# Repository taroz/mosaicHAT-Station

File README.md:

# mosaicHAT-Station
## Introduction
- [**mosaicHAT**](https://github.com/septentrio-gnss/mosaicHAT) + **GNSS antenna** + **Raspberry Pi** + **Touch display** + **Battery** + **Case**
- We use [Septentrio's mosaic-X5](https://www.septentrio.com/en/products/gnss-receivers/rover-base-receivers/receivers-module/mosaic) GNSS module which is a **low-cost** and **survey-grade** GNSS receiver
- This project is inspired by [mosaicHAT](https://github.com/septentrio-gnss/mosaicHAT) and extends it further. Thanks to the wonderful project [mosaicHAT](https://github.com/septentrio-gnss/mosaicHAT)!
- License: [Creative Commons Attribution Share-Alike License](https://creativecommons.org/licenses/by-sa/4.0/). and [Open Source HW](https://www.oshwa.org/definition/)  

## Features
- mosaicHAT Station has a touch display to display a web user interface of mosaic-X5 receiver. We can easily operate, monitor, and control the GNSS receiver.
- Compared to the original [mosaicHAT](https://github.com/septentrio-gnss/mosaicHAT), we added micro SD card and a log button, so you can easily store GNSS data as a GNSS reference or rover station.  

## Board
- The design of the board is based on the original [mosaicHAT](https://github.com/septentrio-gnss/mosaicHAT).
- [KiCAD files](./board/KiCAD) and [PCB](./board/KiCAD/pcb)
- Micro SD card and log button have been added for data logging capability
- Bill of Materials (BOM) is [here](./board/mosaicHAT_BOM.xlsx)                                 

## Case
- You can create using 3D printer (STL data is [here](./case))
  - I used 3D printing service (by [Shapeways](https://www.shapeways.com/shops/tarosuzuki)) 
- A 5/8 nut can be fixed on the case, which can be attached to a pole or antenna mount for GNSS surveying.  

## How to assemble
- Parts list is [here](./case/parts_list.xlsx)  
<p>

1. Mount the Raspberry Pi on the touch display. Then mount the mosaicHAT on the Rasberry Pi using the M2.5 18mm spacers and screws.   
<p>

2. Fix the GNSS antenna using the M2.5 screws. Connect the SMA cable. Mount the touch display on the case using the M2.5 screws.   
<p>

3. Modify the battery holder to connect the DCDC converter to the battery. Fix the battery holder to the back plate. Then connect the power cable to the mosaicHAT. Fix the front plate using the M3 screws.  
<p>

4. Finally, fix the front and back plate using M3 50mm screws. Insert the W5/8 nut to bottom plate. Fix the bottom plate to the case.   
<p> 

## Setup
### Install **Raspberry Pi OS** on Raspberry Pi
- See [here](https://www.raspberrypi.org/software/)

### Setup Toouch Screen
- mosaicHAT-Station uses [Waveshare 4.3inch HDMI LCD(B)](https://www.waveshare.com/4.3inch-hdmi-lcd-b.htm). See the [wiki](https://www.waveshare.com/wiki/4.3inch_HDMI_LCD_(B)) for setup instructions.

### Start web user interface of mosaic-X5
- mosaicHAT-Station uses Raspberry PI kiosk mode with Chromium for the web user interface.
- Install chromium.
```
sudo apt-get update && apt-get upgrade -y
sudo apt-get install chromium x11-xserver-utils
```
- Edit `/etc/xdg/lxsession/LXDE/autostart` and add the following lines:
```
@xset s off
@xset -dpms
@xset s noblank
@chromium --noerrdialogs --kiosk --incognito 192.168.3.1
```

### Make Raspberry Pi file system read-only
- Let's turn off the Raspberry Pi at any time without risk of damaging the operating system files.
- Run `sudo raspi-config`
- Choose "performance options" and then "Overlay File System". Choose "Yes" to enable it, and then choose "Yes" again to make the boot filesystem read-only.

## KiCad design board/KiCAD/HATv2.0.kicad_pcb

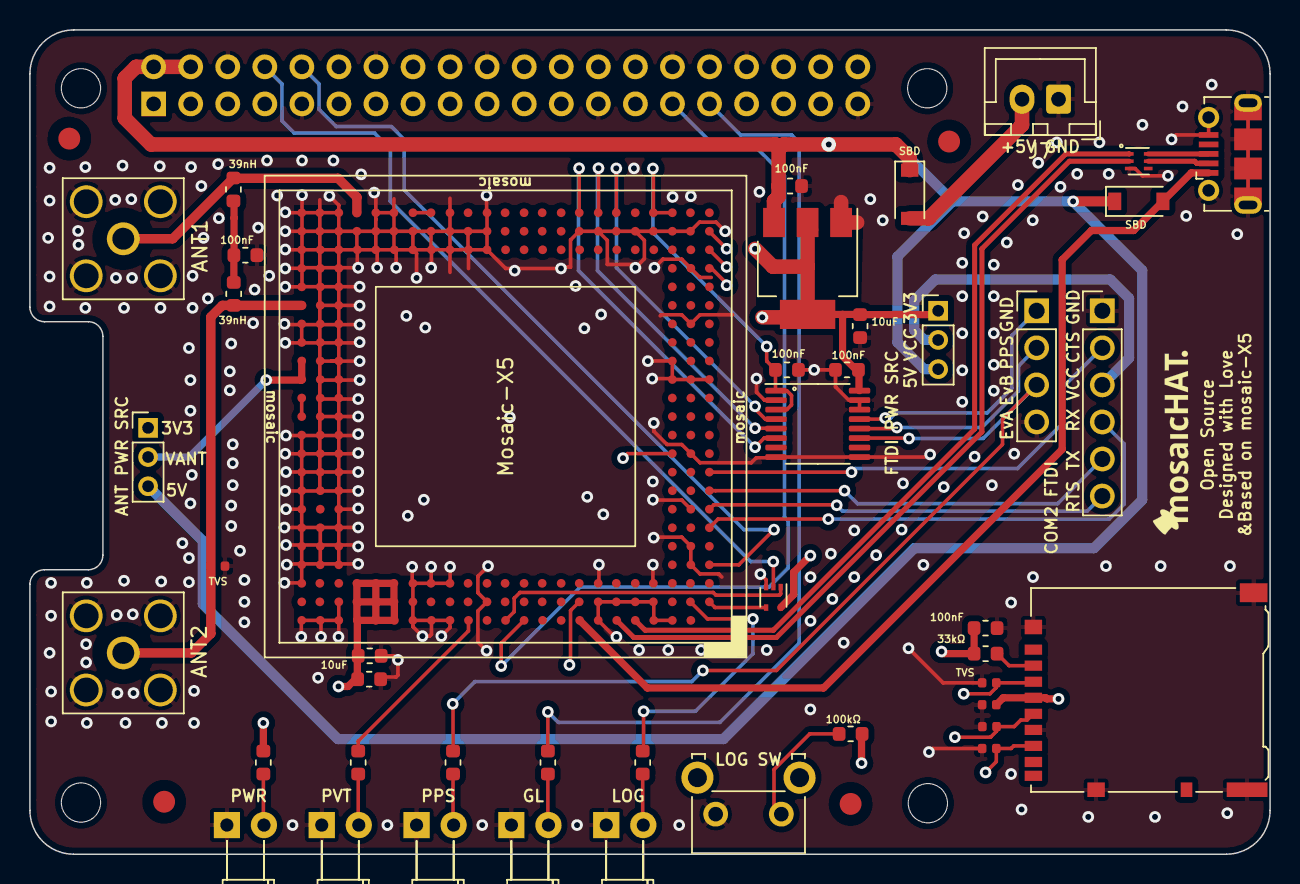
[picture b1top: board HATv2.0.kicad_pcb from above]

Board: 4 copper layers, 85.0 x 56.5 mm, 49 parts (1 on the bottom side), 45 nets.

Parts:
C1, C3, C4, C5, C8: 100nF; C_0603_1608Metric
C2, C6: 10uF; C_0603_1608Metric
C7: un-assembled; C_0603_1608Metric
D1, D2: MBRX120LF-TP; D_SOD-123
D4, D5, D6, D7, D8: LED; LED_D3.0mm_Horizontal_O3.81mm_Z10.0mm
D9, D10, D11, D12, D13: D_TVS; R_0402_1005Metric
FID1, FID2, FID3, FID4: Fiducial; Fiducial_1.5mm_Mask3mm
FL1: ECMF02-2AMX6; ST_UQFN-6L_1.5x1.7mm_Pitch0.5mm
J1, J2: Conn_Coaxial; SMA_Amphenol_132203-12_Horizontal
J3: USB_B_Micro; USB_Micro-B_Molex-105017-0001
J4: raspberrypi_hat_OX40HAT; PinSocket_2x20_P2.54mm_Vertical
J5: Conn_01x04_Male; PinHeader_1x04_P2.54mm_Vertical
J6: Conn_01x06_Male; PinHeader_1x06_P2.54mm_Vertical
J7: Conn_01x02_Male; JST_XH_B2B-XH-A_1x02_P2.50mm_Vertical
J8: Micro_SD_Card_Det_Hirose_DM3AT; microSD_HC_Hirose_DM3AT-SF-PEJM5
JP1, JP2: Jumper_NC_Dual; PinHeader_1x03_P2.00mm_Vertical
L1, L2: 39nH; L_0603_1608Metric
R1, R2, R3, R4, R5: R330; R_0603_1608Metric
R6: R33K; R_0603_1608Metric
R7: R100K; R_0603_1608Metric
SW1: SW_Push; SW_Tactile_SKHH_Angled
U1: mosaic-X5; mosaic_X5
U2: LD1117AS33TR; SOT-223
U3: SN74AVC4T245PW; TSSOP-16_4.4x5mm_P0.65mm
U4: SN74LVC1G126DRLR; SOT-553

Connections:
+1V8: C4.1, U1.AC3, U1.AC4, U3.1, U3.3
+3V3: C2.1, C5.1, C6.1, C7.1, C8.1, D13.2, J8.4, JP1.1, JP2.1, R1.2, R6.2, R7.1, U1.A19, U1.A20, U1.B8, U1.B18, U1.B19, U1.B20, U1.C18, U1.C19, U1.C20, U2.2, U3.16, U4.5
+5V: C1.1, D1.1, D2.1, J4.2, J4.4, JP1.3, JP2.3, U2.3
/2V8: U1.M23, U1.N23
/ANT1: J1.1, L1.1, U1.AC20
/ANT2: D9.2, J2.1, L2.2, U1.V23
/D+: FL1.6, J3.3
/D-: FL1.5, J3.2
/EVENTA_1V8: U1.AC6, U3.4
/EVENTA_3V3: J5.1, U3.13
/EVENTB_1V8: U1.AC7, U3.5
/EVENTB_3V3: J5.2, U3.12
/External_5V: D2.2, J7.2
/FTDI_PWR: J6.3, JP2.2
/GPLED: R5.2, U1.A14
/LOGBUTTON: R7.2, SW1.1, U1.K3
/LOGLED: R4.2, U1.B2
/MODULE_RDY: U1.A12, U4.1
/MosaicCTS2: J6.2, U1.J1
/MosaicRTS2: J6.6, U1.G1
/MosaicRX1: J4.8, U4.2
/MosaicRX1_BufferOUT: U1.B1, U4.4
/MosaicRX2: J6.4, U1.F1
/MosaicTX1: J4.10, U1.D1
/MosaicTX2: J6.5, U1.H1
/PPSO_1V8: U1.AC8, U3.6
/PPSO_3V3: J5.3, R2.2, U3.11
/REF: U1.AC16, U1.AC17
/RPI_GP1: J4.31, R3.2
/SD_CLK: D11.2, J8.5, U1.AA1
/SD_CMD: D10.2, J8.3, U1.AB1
/SD_DAT0: D12.2, J8.7, U1.Y1
/USB_N: FL1.2, U1.A6
/USB_P: FL1.1, U1.A5
/USB_V: D1.2, J3.1, U1.A8
/VANT: JP1.2, U1.P23, U1.R23
/nRST_IN: J4.29, U1.A11
GND: C1.2, C2.2, C3.2, C4.2, C5.2, C6.2, C7.2, C8.2, D4.1, D5.1, D6.1, D7.1, D8.1, D9.1, D10.1, D11.1, D12.1, D13.1, FL1.3, J1.2, J2.2, J3.5, J3.6, J4.6, J4.9, J4.14, J4.20, J4.25, J4.30, J4.34, J4.39, J5.4, J6.1, J7.1, J8.6, J8.11, SW1.2, U1.A3, U1.A4, U1.A7, U1.A15, U1.A16, U1.A17, U1.A21, U1.A22, U1.A23, U1.AA13, U1.AA14, U1.AA15, U1.AA16, U1.AA17, U1.AA18, U1.AA19, U1.AA20, U1.AA21, U1.AA22, U1.AA23, U1.AB2, U1.AB3, U1.AB4, U1.AB5, U1.AB6, U1.AB7, U1.AB8, U1.AB13, U1.AB14, U1.AB15, U1.AB16, U1.AB17, U1.AB18, U1.AB19, U1.AB20, U1.AB21, U1.AB22, U1.AB23, U1.AC13, U1.AC15, U1.AC18, U1.AC19, U1.AC21, U1.AC22, U1.AC23, U1.B4, U1.B5, U1.B6, U1.B7, U1.B13, U1.B17, U1.B21, U1.C4, U1.C7, U1.C15, U1.C16, U1.C17, U1.C23, U1.D2, U1.D21, U1.D22, U1.D23, U1.E2, U1.E21, U1.E22, U1.E23, U1.F21, U1.F22, U1.F23, U1.G2, U1.G21, U1.G23, U1.H21, U1.H22, U1.H23, U1.J21, U1.J22, U1.J23, U1.K2, U1.K21, U1.K22, U1.K23, U1.L21, U1.L22, U1.L23, U1.M21, U1.M22, U1.N21, U1.N22, U1.P1, U1.P2, U1.P3, U1.P21, U1.P22, U1.R3, U1.R21, U1.R22, U1.T21, U1.T22, U1.T23, U1.U2, U1.U21, U1.U22, U1.U23, U1.V21, U1.V22, U1.W21, U1.W22, U1.W23, U1.Y2, U1.Y21, U1.Y22, U1.Y23, U2.1, U3.2, U3.8, U3.9, U3.14, U3.15, U4.3
unnamed: C3.1, L1.2, L2.1
unnamed: D4.2, R1.1
unnamed: D5.2, R2.1
unnamed: D6.2, R3.1
unnamed: D7.2, R4.1
unnamed: D8.2, R5.1
unnamed: J8.2, R6.1

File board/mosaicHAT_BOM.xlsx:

Reference | Quantity | Value | MPN | SPN | Digi-Key URL
C2 C6 | 2 | 10uF | CC0603KRX5R6BB106 | 311-1782-1-ND | https://www.digikey.com/product-detail/en/yageo/CC0603KRX5R6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
C1 C3 C4 C5 C8 | 5 | 100nF | CC0603KRX7R6BB104 | 311-4055-1-ND | https://www.digikey.com/product-detail/en/yageo/CC0603KRX7R6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
D1 D2 | 2 | MBRX120LF-TP | MBRX120LF-TP | MBRX120LF-TPMSCT-ND | https://www.digikey.com/product-detail/en/micro-commercial-c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
D4 D5 D6 D7 D8 | 5 | LED | 151031VS06000 | 732-5008-ND | https://www.digikey.com/en/products/detail/w%C3%BCrth-elektr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
D9 D10 D11 D12 D13 | 5 | D_TVS | SESD0402X1BN-0010-098 | SESD0402X1BN-0010-098CT-ND | https://www.digikey.com/en/products/detail/littelfuse-inc/SE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
FL1 | 1 | ECMF02-2AMX6 | ECMF02-2AMX6 | 497-10773-1-ND | https://www.digikey.com/product-detail/en/stmicroelectronics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
J1 J2 | 2 | Conn_Coaxial | 132136 | ACX1232-ND | https://www.digikey.com/product-detail/en/amphenol-rf/132136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
J3 | 1 | USB_B_Micro | 1050170001 | WM1399CT-ND | https://www.digikey.com/product-detail/en/molex/1050170001/W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
J4 | 1 | raspberrypi_hat_OX40HAT | PRT-14017 | 1568-1462-ND | https://www.digikey.com/en/products/detail/sparkfun-electron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
J5 | 1 | Conn_01x04_Male | 61300411121 | 732-5317-ND | https://www.digikey.com/product-detail/en/w%C3%BCrth-elektro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
J6 | 1 | Conn_01x06_Male | 61300611121 | 732-5319-ND | https://www.digikey.com/product-detail/en/w%C3%BCrth-elektro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
J7 | 1 | Conn_01x02_Male | B2B-XH-A(LF)(SN) | 455-2247-ND | https://www.digikey.com/en/products/detail/jst-sales-america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
J8 | 1 | Micro_SD_Card | DM3AT-SF-PEJM5 | HR1964CT-ND | https://www.digikey.com/en/products/detail/hirose-electric-c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
JP1 JP2 | 2 | Jumper_NC_Dual | 2PH1-03-UA | 2057-2PH1-03-UA-ND | https://www.digikey.com/product-detail/en/adam-tech/2PH1-03-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
L1 L2 | 2 | 39nH | 744786139A | 732-6270-1-ND | https://www.digikey.com/product-detail/en/w%C3%BCrth-elektro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
R1 R2 R3 R4 R5 | 5 | R330 | ERJ-3EKF3300V | P330HCT-ND | https://www.digikey.com/product-detail/en/panasonic-electron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
R6 | 1 | R33K | ERJ-3EKF3302V | P33.0KHCT-ND | https://www.digikey.com/en/products/detail/panasonic-electro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
R7 | 1 | 100K | ERJ-U3RD1003V | 10-ERJ-U3RD1003VCT-ND | https://www.digikey.com/en/products/detail/panasonic-electro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
U1 | 1 | mosaic-X5 | 410322 | 2771-410322-ND | https://www.digikey.com/en/products/detail/septentrio-inc/41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
U2 | 1 | LD1117AS33TR | LD1117AS33TR | 497-1228-1-ND | https://www.digikey.com/product-detail/en/stmicroelectronics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
U3 | 1 | SN74AVC4T245PW | SN74AVC4T245PWR | 296-18056-1-ND | https://www.digikey.com/product-detail/en/texas-instruments/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
U4 | 1 | SN74LVC1G126DRLR | SN74LVC1G126DRLR | 296-18013-1-ND | https://www.digikey.com/product-detail/en/texas-instruments/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

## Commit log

2021-02-10 Change README
2021-02-10 Change file names
2021-02-10 Update mosaicHAT.gif
    Replace gif file
